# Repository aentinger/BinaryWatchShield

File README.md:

💾 Binary Watch Shield
======================

# 📸 Image

# 📂 Description

There are only 10 types of people in the world: those who understand binary, and those who don't (haha ;P). If you are among the people who do not understand this computer joke, then the LXRobotics Binary Watch Shield is just the thing for you. In conjunction with an Arduino, the Binary Watch Shield may in fact be used to display the current time in binary format. Thereby, learning binary code will become a child's play. For the quick start, a finished Arduino Library with a binary clock sample program is available.

**Features**

* Display of the current time (HH:MM) in binary format using red, orange and green LEDs
* I2C-Real Time Clock  (RTC) for the watch functionality
* Arduino Library available for control with binary clock example programms

# 🎥 [Video](images/binary_watch_shield_demo.mp4)

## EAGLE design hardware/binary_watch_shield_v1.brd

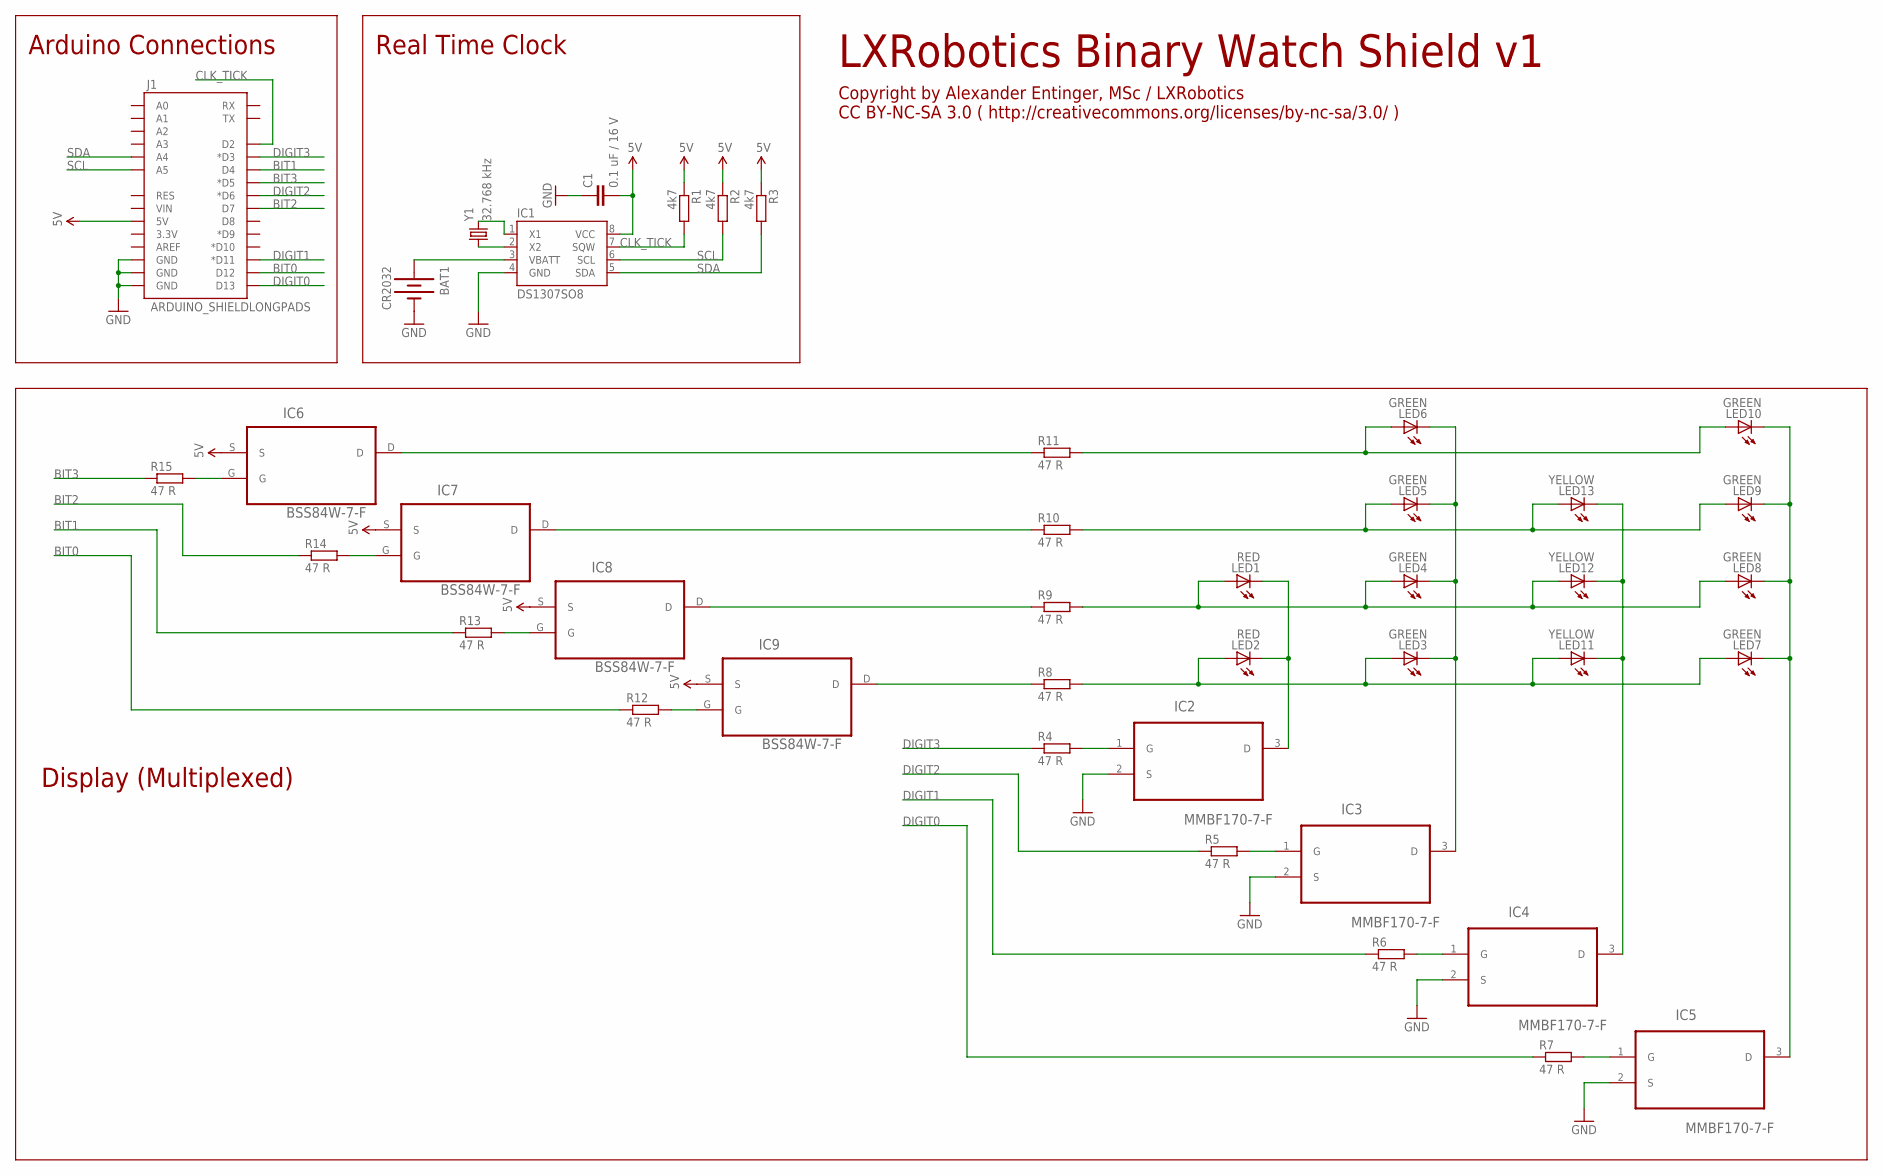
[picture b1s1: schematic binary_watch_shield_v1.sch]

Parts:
BAT1: CR2032; BATTCON_20MM
C1: 0.1 uF / 16 V; C0805
IC1: DS1307SO8; SO08
IC2, IC3, IC4, IC5: MMBF170-7-F; SOT103P240X110-3N
IC6, IC7, IC8, IC9: BSS84W-7-F; SOT65P210X110-3N
J1: ARDUINO_SHIELDLONGPADS; DUEMILANOVE_SHIELD_LONGPADS
LED1, LED2: RED; LED5MM
LED3, LED4, LED5, LED6, LED7, LED8, LED9, LED10: GREEN; LED5MM
LED11, LED12, LED13: YELLOW; LED5MM
R1, R2, R3: 4k7; R0805
R4, R5, R6, R7, R8, R9, R10, R11, R12, R13, R14, R15: 47 R; R0805
Y1: 32.768 kHz; TC26HEZ

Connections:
5V: C1.2, IC1.8 (VCC), IC6.S, IC7.S, IC8.S, IC9.S, J1.5V, R1.1, R2.1, R3.1
BIT0: J1.D12, R12.1
BIT1: J1.D4, R13.1
BIT2: J1.D7, R14.1
BIT3: J1.D5 (*D5), R15.1
CLK_TICK: IC1.7 (SQW), J1.D2, R1.2
DIGIT0: J1.D13, R7.1
DIGIT1: J1.D11 (*D11), R6.1
DIGIT2: J1.D6 (*D6), R5.1
DIGIT3: J1.D3 (*D3), R4.1
GND: BAT1.2 (-), C1.1, IC1.4 (GND), IC2.2 (S), IC3.2 (S), IC4.2 (S), IC5.2 (S), J1.GND@0 (GND), J1.GND@1 (GND), J1.GND@2 (GND)
unnamed: IC2.3 (D), LED1.K (C), LED2.K (C)
unnamed: IC3.3 (D), LED3.K (C), LED4.K (C), LED5.K (C), LED6.K (C)
unnamed: IC4.3 (D), LED11.K (C), LED12.K (C), LED13.K (C)
unnamed: IC1.2 (X2), Y1.1
unnamed: IC1.1 (X1), Y1.2
unnamed: IC5.3 (D), LED7.K (C), LED8.K (C), LED9.K (C), LED10.K (C)
unnamed: LED5.A, LED9.A, LED13.A, R10.2
unnamed: LED2.A, LED3.A, LED7.A, LED11.A, R8.2
unnamed: LED1.A, LED4.A, LED8.A, LED12.A, R9.2
unnamed: LED6.A, LED10.A, R11.2
unnamed: IC2.1 (G), R4.2
unnamed: IC3.1 (G), R5.2
unnamed: IC4.1 (G), R6.2
unnamed: IC5.1 (G), R7.2
unnamed: IC9.D, R8.1
unnamed: IC8.D, R9.1
unnamed: IC7.D, R10.1
unnamed: IC6.D, R11.1
unnamed: IC6.G, R15.2
unnamed: IC7.G, R14.2
unnamed: IC8.G, R13.2
unnamed: IC9.G, R12.2
unnamed: BAT1.1 (+), IC1.3 (VBATT)
SCL: IC1.6 (SCL), J1.A5, R2.2
SDA: IC1.5 (SDA), J1.A4, R3.2

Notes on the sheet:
Copyright by Alexander Entinger, MSc / LXRobotics CC BY-NC-SA 3.0 ( http://creativecommons.org/licenses/by-nc-sa/3.0/ )
LXRobotics Binary Watch Shield v1
Arduino Connections
Real Time Clock
Display (Multiplexed)

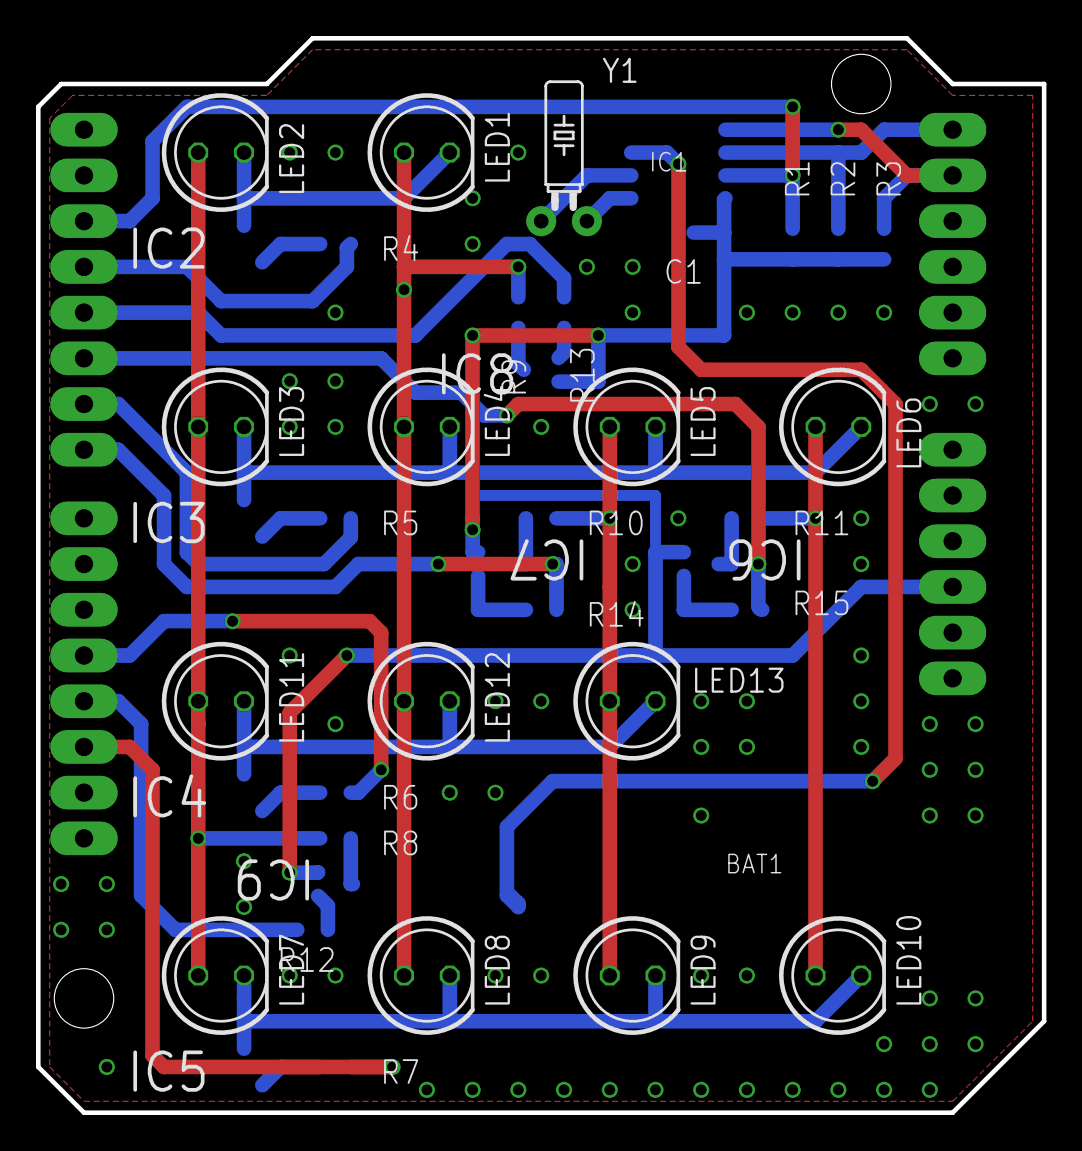
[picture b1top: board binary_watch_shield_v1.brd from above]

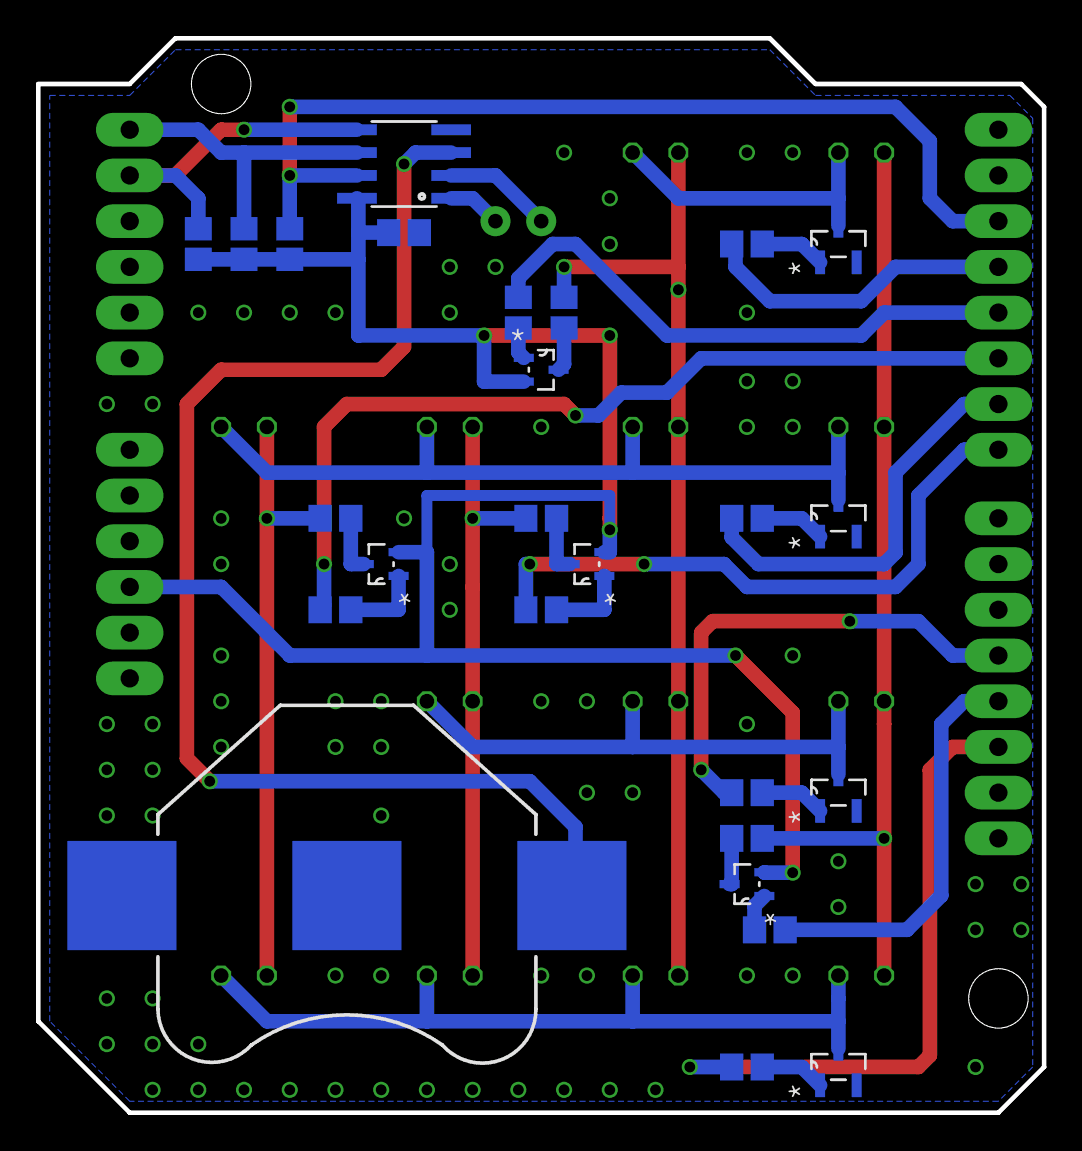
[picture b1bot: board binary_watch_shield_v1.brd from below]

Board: 2 copper layers, 55.9 x 59.7 mm, 41 parts (26 on the bottom side), 36 nets.

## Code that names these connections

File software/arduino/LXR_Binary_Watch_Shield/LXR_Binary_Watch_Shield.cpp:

/**
 * @author Alexander Entinger, MSc / LXRobotics
 * @brief this module implements the library for controlling the LXRobotics Binary Watch Shield
 * @file LXR_Binary_Watch_Shield.cpp
 * @license Attribution-NonCommercial-ShareAlike 3.0 Unported (CC BY-NC-SA 4.0) ( https://creativecommons.org/licenses/by-nc-sa/4.0/ )
 */
 
#include "LXR_Binary_Watch_Shield.h"

/* C CODE */

/* INCLUDES */

#include <avr/io.h>
#include <avr/interrupt.h>

/* DEFINES */

// DIGIT0 = D13 = PB5
#define DIGIT_0_DDR		(DDRB)
#define DIGIT_0_PORT	(PORTB)
#define DIGIT_0_bm		(1<<PORTB5)
// DIGIT1 = D11 = PB3
#define DIGIT_1_DDR		(DDRB)
#define DIGIT_1_PORT	(PORTB)
#define DIGIT_1_bm		(1<<PORTB3)
// DIGIT2 = D6 = PD6
#define DIGIT_2_DDR		(DDRD)
#define DIGIT_2_PORT	(PORTD)
#define DIGIT_2_bm		(1<<PORTD6)
// DIGIT3 = D3 = PD3
#define DIGIT_3_DDR		(DDRD)
#define DIGIT_3_PORT	(PORTD)
#define DIGIT_3_bm		(1<<PORTD3)
// BIT0 = D12 = PB4
#define BIT_0_DDR		(DDRB)
#define BIT_0_PORT		(PORTB)
#define BIT_0_bm		(1<<PORTB4)
// BIT1 = D4 = PD4
#define BIT_1_DDR		(DDRD)
#define BIT_1_PORT		(PORTD)
#define BIT_1_bm		(1<<PORTD4)
// BIT2 = D7 = PD7
#define BIT_2_DDR		(DDRD)
#define BIT_2_PORT		(PORTD)
#define BIT_2_bm		(1<<PORTD7)
// BIT3 = D5 = PD5
#define BIT_3_DDR		(DDRD)
#define BIT_3_PORT		(PORTD)
#define BIT_3_bm		(1<<PORTD5)

/* TYPEDEFS */

typedef enum {DIGIT0 = 0, DIGIT1 = 1, DIGIT2 = 2, DIGIT3 = 3} E_DIGIT_SELECT;

typedef struct 
{
	uint8_t current_digit;
	uint8_t display_data[4];
} s_binary_watch_shield_data; 

/* GLOBAL CONSTANTS */

static uint16_t const TIMER1_RELOAD_VALUE = 0xC180;

/* GLOBAL VARIABLES */

static s_binary_watch_shield_data bws_data = {0};

/* PROTOTYPES */

void set_digit(E_DIGIT_SELECT const digit, uint8_t const val);

/* FUNCTIONS */

/** 
 * @brief initializes the binary watch shield
 */
void init_binary_watch_shield()
{
	// set all pins as outputs
	DIGIT_0_DDR |= DIGIT_0_bm;
	DIGIT_1_DDR |= DIGIT_1_bm;
	DIGIT_2_DDR |= DIGIT_2_bm;
	DIGIT_3_DDR |= DIGIT_3_bm;
	
	BIT_0_DDR |= BIT_0_bm;
	BIT_1_DDR |= BIT_1_bm;
	BIT_2_DDR |= BIT_2_bm;
	BIT_3_DDR |= BIT_3_bm;
	
	// set up timer 1
	// fclk = 16 MHz, prescaler = 1, fTimer = 16 MHz, tTimer = 62.5 ns
	// tUpdate,Period = 1 ms -> 16000 Timersteps
	// Reload-Wert = 65536 - 16000 = 0xC180
	TCNT1 = TIMER1_RELOAD_VALUE;
	// enable overflow interrupt
	TIMSK1 = (1<<TOIE1);
	// start timer
	TCCR1B = (1<<CS10);	
}

/** 
 * @brief set the numbers for the binary watch shield to display
 */
void binary_watch_shield_set_display(uint8_t const digit_3, uint8_t const digit_2, uint8_t const digit_1, uint8_t const digit_0)
{
	cli();
	bws_data.display_data[DIGIT0] = digit_0;
	bws_data.display_data[DIGIT1] = digit_1;
	bws_data.display_data[DIGIT2] = digit_2;
	bws_data.display_data[DIGIT3] = digit_3;
	sei();
}

void set_digit(E_DIGIT_SELECT const digit, uint8_t const val)
{
	// switch all digits off
	DIGIT_0_PORT &= ~DIGIT_0_bm;
	DIGIT_1_PORT &= ~DIGIT_1_bm;
	DIGIT_2_PORT &= ~DIGIT_2_bm;
	DIGIT_3_PORT &= ~DIGIT_3_bm;
	
	// display value on the bit lines
	uint8_t tmp = val;
	if(tmp % 2) BIT_0_PORT &= ~BIT_0_bm;
	else BIT_0_PORT |= BIT_0_bm;
	tmp /= 2;
	if(tmp % 2) BIT_1_PORT &= ~BIT_1_bm;
	else BIT_1_PORT |= BIT_1_bm;
	tmp /= 2;
	if(tmp % 2) BIT_2_PORT &= ~BIT_2_bm;
	else BIT_2_PORT |= BIT_2_bm;
	tmp /= 2;
	if(tmp % 2) BIT_3_PORT &= ~BIT_3_bm;
	else BIT_3_PORT |= BIT_3_bm;
	
	// switch the selected digit on
	switch(digit)
	{
		case DIGIT0: DIGIT_0_PORT |= DIGIT_0_bm; break;		
		case DIGIT1: DIGIT_1_PORT |= DIGIT_1_bm; break;
		case DIGIT2: DIGIT_2_PORT |= DIGIT_2_bm; break;
		case DIGIT3: DIGIT_3_PORT |= DIGIT_3_bm; break;
		default: break;
	}
}

/** 
 * @brief Interrupt Service Routine for Timer 1 Overflow
 */
ISR(TIMER1_OVF_vect)
{
	// reload timer
	TCNT1 = TIMER1_RELOAD_VALUE;
	
	// set the digit
	set_digit(E_DIGIT_SELECT(bws_data.current_digit), bws_data.display_data[bws_data.current_digit]);
	
	// update current digit state
	bws_data.current_digit = (bws_data.current_digit + 1) % 4;
}

/* CPP WRAPPER */

/** 
 * @brief initializes the library
 */
void LXR_Binary_Watch_Shield::begin()
{
  init_binary_watch_shield();
}
  
/**
 * @brief sets what number should be displayed on which digit of the binary watch shield
 */
void LXR_Binary_Watch_Shield::set_display(uint8_t const digit_3, uint8_t const digit_2, uint8_t const digit_1, uint8_t const digit_0)
{
  binary_watch_shield_set_display(digit_3, digit_2, digit_1, digit_0);
}

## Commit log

2015-03-03 initial checkin of lxrobotics binary watch shield
2015-03-24 bugfix in binary watch shield library
2017-06-27 Adding hardware + images
2025-03-26 Pretty up README.
2025-03-26 Upload video file.
2025-03-26 Add link to video.
2025-03-26 Add BOM.
2025-03-26 Use relative link.

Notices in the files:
README.md:
License: CC BY-NC-SA 4.0
parts and their libraries:
SparkFun-Boards: Licensing: CC v3.0 Share-Alike You are welcome to use this library for commercial purposes.
